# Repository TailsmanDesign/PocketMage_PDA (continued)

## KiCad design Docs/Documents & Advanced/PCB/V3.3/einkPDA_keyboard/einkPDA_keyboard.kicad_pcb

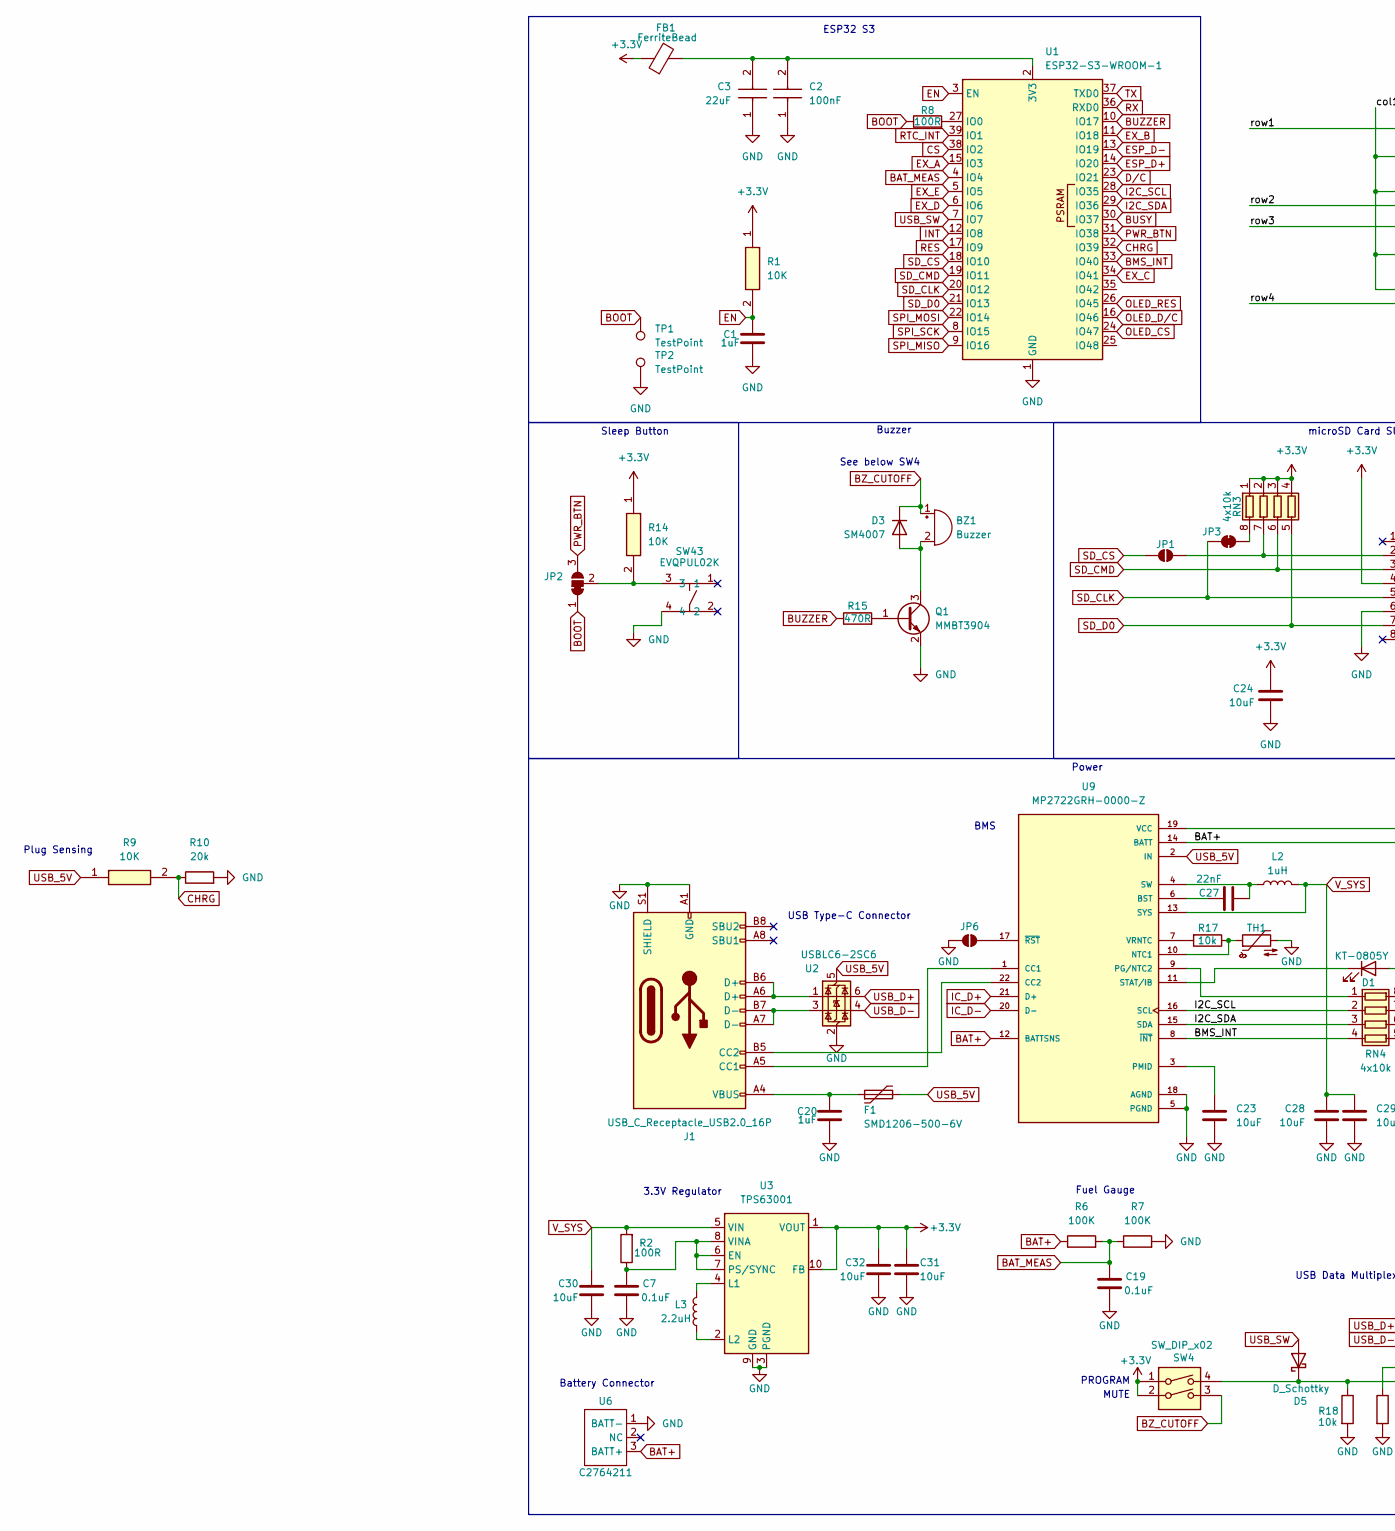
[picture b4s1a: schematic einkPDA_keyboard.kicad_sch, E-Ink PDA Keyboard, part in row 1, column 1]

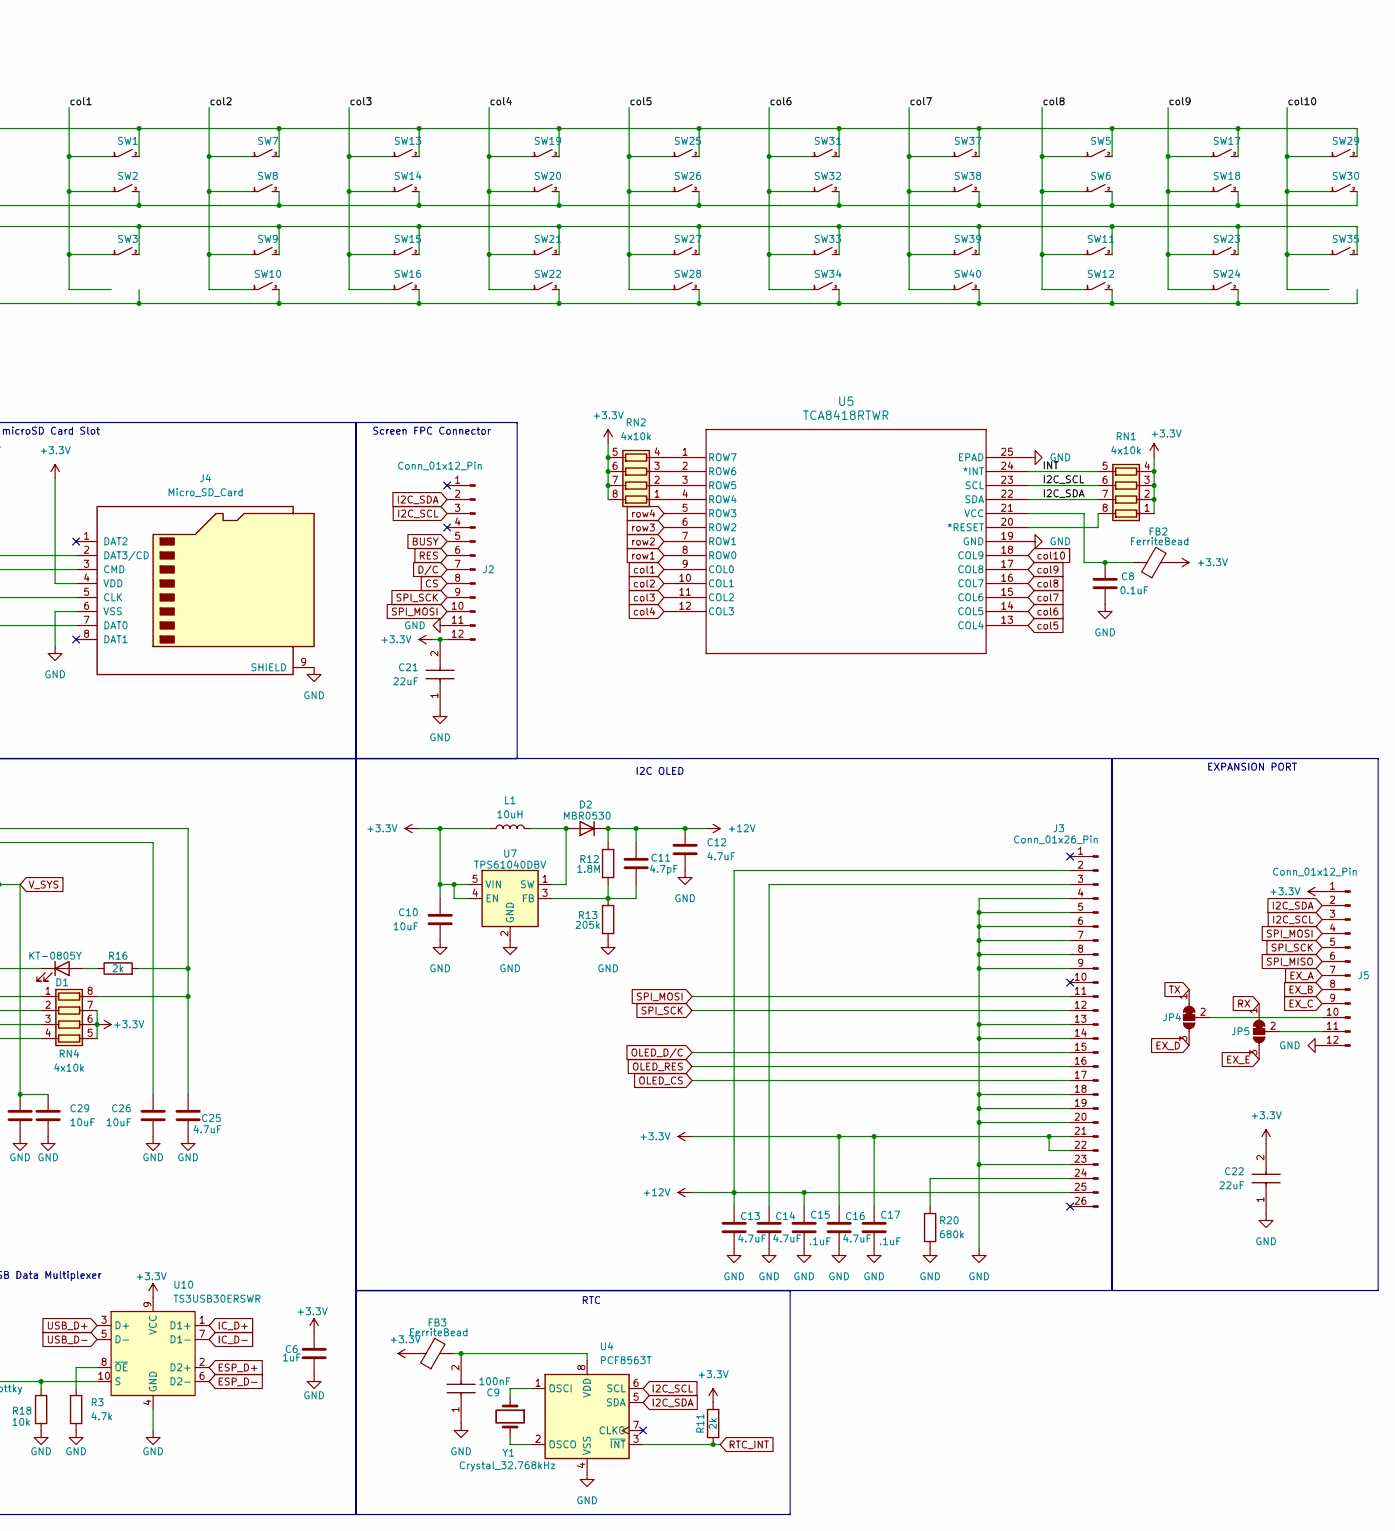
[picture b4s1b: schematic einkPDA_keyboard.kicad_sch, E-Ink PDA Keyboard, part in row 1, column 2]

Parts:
BZ1: Buzzer; BUZ-SMD_3P_L5.0-W5.0-P3.50-TL; LCSC Part # C781883
C1, C6, C20: 1uF; C_0603_1608Metric; LCSC Part # C15849
C2, C9: 100nF; C_0805_2012Metric; Mouser Part Number 603-CC805KRX7R9BB104
C3, C21, C22: 22uF; C_0805_2012Metric; Mouser Part Number 187-CL21A226MAQNNNE
C7, C8, C19: 0.1uF; C_0402_1005Metric; LCSC Part # C1525
C10, C23, C26, C28, C29, C30, C31, C32: 10uF; C_0805_2012Metric; LCSC PART # C15850
C11: 4.7pF; C_0603_1608Metric; LCSC PART # C1669
C12, C13, C14, C16: 4.7uF; C_1206_3216Metric; LCSC PART # C29823
C15, C17: .1uF; C_0805_2012Metric; LCSC PART # C28233
C24: 10uF; C_0805_2012Metric; LCSC Part # C15850
C25: 4.7uF; C_0805_2012Metric; LCSC Part # C1779
C27: 22nF; C_0603_1608Metric; LCSC Part # C21122
D1: KT-0805Y; LED_0805_2012Metric; LCSC Part # C2296
D2: MBR0530; D_SOD-123; LCSC PART # C77336
D3: SM4007; D_SOD-123F; LCSC Part # C64898
D5: D_Schottky; D_SOD-323; LCSC Part # C191023
F1: SMD1206-500-6V; Fuse_1206_3216Metric; LCSC Part # C2760308
FB1, FB2, FB3: FerriteBead; L_0603_1608Metric; LCSC Part # C85831
J1: USB_C_Receptacle_USB2.0_16P; USB-TYPE-C-SMD_TYPE-C-16P-QTWT; LCSC Part # C5187472
J2, J5: Conn_01x12_Pin; AFC01-S12FCA-00; LCSC Part # C262661
J3: Conn_01x26_Pin; FPC-SMD_AFC24-S26FIA [DUAL-SIDE]; LCSC PART # C262684
J4: Micro_SD_Card; TF-SMD_503398-1892; LCSC Part # C428492
JP1, JP6: SolderJumper_2_Open; SolderJumper-2_P1.3mm_Open_RoundedPad1.0x1.5mm
JP2, JP4, JP5: SolderJumper_3_Bridged12; SolderJumper-3_P1.3mm_Bridged12_RoundedPad1.0x1.5mm
JP3: SolderJumper_2_Bridged; SolderJumper-2_P1.3mm_Bridged_RoundedPad1.0x1.5mm
L1: 10uH; L_Chilisin_BMRx00060630; LCSC PART # C5189958
L2: 1uH; L_Ferrocore_DLG-0504; LCSC Part # C2929426
L3: 2.2uH; L_Wurth_WE-LQSH-3012; LCSC Part # C19734
Q1: MMBT3904; SOT-23; LCSC Part # C20526
R1, R9, R14: 10K; R_0805_2012Metric; Mouser Part Number 303-0805W8F1002T5E
R2, R8: 100R; R_0603_1608Metric; LCSC Part # C22775
R3: 4.7k; R_0603_1608Metric; LCSC Part # C23162
R6, R7: 100K; R_0603_1608Metric; LCSC Part # C25803
R10: 20k; R_0603_1608Metric; LCSC Part # C4184
R11, R16: 2k; R_0805_2012Metric; LCSC Part # C17604
R12: 1.8M; R_0805_2012Metric; LCSC PART # C17399
R13: 205k; R_0805_2012Metric; LCSC PART # C218417
R15: 470R; R_0805_2012Metric; LCSC Part # C17710
R17: 10k; R_0805_2012Metric; LCSC Part # C17414
R18: 10k; R_0603_1608Metric; LCSC Part # C25804
R20: 680k; R_0805_2012Metric; LCSC PART # C17797
RN1, RN2, RN3, RN4: 4x10k; R_Array_Concave_4x0603; LCSC Part # C29718
SW1, SW2, SW3, SW5, SW6, SW7, SW8, SW9, SW10, SW11, SW12, SW13, SW14, SW15, SW16, SW17, SW18, SW19, SW20, SW21, SW22, SW23, SW24, SW25, SW26, SW27, SW28, SW29, SW30, SW31, SW32, SW33, SW34, SW35, SW37, SW38, SW39, SW40: contact_pad_SINGLE
SW4: SW_DIP_x02; 2X_DIP_DHN-02-V-TR; LCSC Part # C224995
SW43: EVQPUL02K; SW-SMD_TS24CA; LCSC Part # C393942
TH1: NTC; R_0603_1608Metric; LCSC Part # C76589
TP1, TP2: TestPoint; TestPoint_Pad_1.0x1.0mm
U1: ESP32-S3-WROOM-1; LCSC Part # C2913202
U2: USBLC6-2SC6; SOT-23-6; LCSC Part # C7519
U3: TPS63001; Texas_DRC0010J_ThermalVias; LCSC Part # C28060
U4: PCF8563T; SOIC-8_3.9x4.9mm_P1.27mm; LCSC Part # C7440
U5: TCA8418RTWR; RTW24_2P45X2P45; LCSC Part # C138713
U6: C2764211; JST_PH_2P_P2.00mm; LCSC Part # C2764211
U7: TPS61040DBV; SOT-23-5; LCSC PART # C7722
U9: MP2722GRH-0000-Z; IC_MP2722GRH-0000-Z; PARTREV 1.0; LCSC Part # C20099551
U10: TS3USB30ERSWR; UQFN-10_1.4x1.8mm_P0.4mm; LCSC Part # C73880
Y1: Crystal_32.768kHz; Crystal_SMD_3215-2Pin_3.2x1.5mm; LCSC Part # C5213671

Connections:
+3.3V: C6.2, C10.2, C16.1, C17.1, C21.2, C22.2, C24.1, C31.2, C32.2, FB1.1, FB2.2, FB3.1, J2.12, J3.21, J3.22, J4.4 (VDD), J5.1, L1.1, R1.1, R11.2, R14.1, RN1.1 (R1.1), RN1.2 (R2.1), RN1.3 (R3.1), RN1.4 (R4.1), RN2.5 (R4.2), RN2.6 (R3.2), RN2.7 (R2.2), RN2.8 (R1.2), RN3.1 (R1.1), RN3.2 (R2.1), RN3.3 (R3.1), RN3.4 (R4.1), RN4.5 (R4.2), RN4.6 (R3.2), RN4.7 (R2.2), SW4.1, SW4.2, U3.1 (VOUT), U3.10 (FB), U7.4 (EN), U7.5 (VIN), U10.9 (VCC)
+12V: C11.2, C12.1, C13.1, C15.1, D2.1 (K), J3.2, J3.25, R12.1
BAT+: C26.2, R6.1, U6.3 (BATT+), U9.12 (BATTSNS), U9.14 (BATT)
BAT_MEAS: C19.1, R6.2, R7.1, U1.4 (IO4)
BMS_INT: RN4.4 (R4.1), U1.33 (IO40), U9.8 (~INT)
BOOT: JP2.1 (A), R8.1, TP1.1
BUSY: J2.5, U1.30 (IO37)
BUZZER: R15.1, U1.10 (IO17)
BZ_CUTOFF: BZ1.1 (+), D3.1 (K), SW4.3
CHRG: R9.2, R10.1, U1.32 (IO39)
CS: J2.8, U1.38 (IO2)
D/C: J2.7, U1.23 (IO21)
EN: C1.2, R1.2, U1.3 (EN)
ESP_D+: U1.14 (IO20), U10.2 (D2+)
ESP_D-: U1.13 (IO19), U10.6 (D2-)
EX_A: J5.7, U1.15 (IO3)
EX_B: J5.8, U1.11 (IO18)
EX_C: J5.9, U1.34 (IO41)
EX_D: JP4.3 (B), U1.6 (IO6)
EX_E: JP5.3 (B), U1.5 (IO5)
GND: C1.1, C2.1, C3.1, C6.1, C7.2, C8.2, C9.1, C10.1, C12.2, C13.2, C14.2, C15.2, C16.2, C17.2, C19.2, C20.1, C21.1, C22.1, C23.1, C24.2, C25.2, C26.1, C28.1, C29.1, C30.1, C31.1, C32.1, J1.A1 (GND), J1.A12 (GND), J1.B1 (GND), J1.B12 (GND), J1.S1 (SHIELD), J2.11, J3.4, J3.5, J3.6, J3.7, J3.8, J3.9, J3.13, J3.14, J3.18, J3.19, J3.20, J3.23, J4.6 (VSS), J4.9 (SHIELD), J5.12, JP6.1 (A), Q1.2 (E), R3.2, R7.2, R10.2, R13.2, R18.2, R20.2, SW43.4, TH1.2, TP2.1, U1.1 (GND), U1.40 (GND), U1.41 (GND), U2.2 (GND), U3.3 (PGND), U3.9 (GND), U3.11 (PGND), U4.4 (VSS), U5.19 (GND), U5.25 (EPAD), U5.V, U6.1 (BATT-), U7.2 (GND), U9.5 (PGND), U9.18 (AGND), U10.4 (GND)
I2C_SCL: J2.3, J5.3, RN1.6 (R3.2), RN4.2 (R2.1), U1.28 (IO35), U4.6 (SCL), U5.23 (SCL), U9.16 (SCL)
I2C_SDA: J2.2, J5.2, RN1.7 (R2.2), RN4.3 (R3.1), U1.29 (IO36), U4.5 (SDA), U5.22 (SDA), U9.15 (SDA)
IC_D+: U9.21 (D+), U10.1 (D1+)
IC_D-: U9.20 (D-), U10.7 (D1-)
INT: RN1.5 (R4.2), U1.12 (IO8), U5.24 (*INT)
unnamed: BZ1.2 (-), D3.2 (A), Q1.3 (C)
unnamed: C20.2, F1.1, J1.A4 (VBUS), J1.A9 (VBUS), J1.B4 (VBUS), J1.B9 (VBUS)
unnamed: D1.2 (A), R16.1
unnamed: D1.1 (K), U9.11 (STAT/IB)
unnamed: D2.2 (A), L1.2, U7.1 (SW)
unnamed: D5.1 (K), R18.1, SW4.4, U10.10 (S)
unnamed: J1.A5 (CC1), U9.1 (CC1)
unnamed: J1.B5 (CC2), U9.22 (CC2)
unnamed: J1.A6 (D+), J1.B6 (D+), U2.1 (I/O1)
unnamed: J1.A7 (D-), J1.B7 (D-), U2.3 (I/O2)
unnamed: C14.1, J3.3
unnamed: J3.24, R20.1
unnamed: J4.2 (DAT3/CD), JP1.2 (B), RN3.7 (R2.2)
unnamed: J5.10, JP4.2 (C)
unnamed: J5.11, JP5.2 (C)
unnamed: JP2.2 (C), R14.2, SW43.3
unnamed: JP3.2 (B), RN3.8 (R1.2)
unnamed: JP6.2 (B), U9.17 (~RST)
unnamed: Q1.1 (B), R15.2
unnamed: RN1.8 (R1.2), U5.20 (*RESET)
unnamed: RN2.1 (R1.1), U5.4 (ROW4)
unnamed: RN2.2 (R2.1), U5.3 (ROW5)
unnamed: RN2.3 (R3.1), U5.2 (ROW6)
unnamed: RN2.4 (R4.1), U5.1 (ROW7)
unnamed: RN4.1 (R1.1), U9.9 (PG/NTC2)
unnamed: C25.1, R16.2, RN4.8 (R1.2), U9.19 (VCC)
unnamed: C2.2, C3.2, FB1.2, U1.2 (3V3)
unnamed: R8.2, U1.27 (IO0)
unnamed: C7.1, R2.1, U3.6 (EN), U3.7 (PS/SYNC), U3.8 (VINA)
unnamed: L3.1, U3.4 (L1)
unnamed: L3.2, U3.2 (L2)
unnamed: U4.1 (OSCI), Y1.1
unnamed: U4.2 (OSCO), Y1.2
unnamed: C9.2, FB3.2, U4.8 (VDD)
unnamed: C8.1, FB2.1, U5.21 (VCC)
unnamed: C11.1, R12.2, R13.1, U7.3 (FB)
unnamed: C27.2, U9.6 (BST)
unnamed: R17.1, TH1.1, U9.10 (NTC1)
unnamed: C23.2, U9.3 (PMID)
unnamed: C27.1, L2.1, U9.4 (SW)
unnamed: R17.2, U9.7 (VRNTC)
unnamed: R3.1, U10.8 (~OE)
OLED_CS: J3.17, U1.24 (IO47)
OLED_D/C: J3.15, U1.16 (IO46)
OLED_RES: J3.16, U1.26 (IO45)
PWR_BTN: JP2.3 (B), U1.31 (IO38)
RES: J2.6, U1.17 (IO9)
RTC_INT: R11.1, U1.39 (IO1), U4.3 (~INT)
RX: JP5.1 (A), U1.36 (RXD0)
SD_CLK: J4.5 (CLK), JP3.1 (A), U1.20 (IO12)
SD_CMD: J4.3 (CMD), RN3.6 (R3.2), U1.19 (IO11)
SD_CS: JP1.1 (A), U1.18 (IO10)
SD_D0: J4.7 (DAT0), RN3.5 (R4.2), U1.21 (IO13)
SPI_MISO: J5.6, U1.9 (IO16)
SPI_MOSI: J2.10, J3.11, J5.4, U1.22 (IO14)
SPI_SCK: J2.9, J3.12, J5.5, U1.8 (IO15)
TX: JP4.1 (A), U1.37 (TXD0)
USB_5V: F1.2, R9.1, U2.5 (VBUS), U9.2 (IN)
USB_D+: U2.6 (I/O1), U10.3 (D+)
USB_D-: U2.4 (I/O2), U10.5 (D-)
USB_SW: D5.2 (A), U1.7 (IO7)
V_SYS: C28.2, C29.2, C30.2, L2.2, R2.2, U3.5 (VIN), U9.13 (SYS)
col1: SW1.1, SW2.1, SW3.1, U5.9 (COL0)
col2: SW7.1, SW8.1, SW9.1, SW10.1, U5.10 (COL1)
col3: SW13.1, SW14.1, SW15.1, SW16.1, U5.11 (COL2)
col4: SW19.1, SW20.1, SW21.1, SW22.1, U5.12 (COL3)
col5: SW25.1, SW26.1, SW27.1, SW28.1, U5.13 (COL4)
col6: SW31.1, SW32.1, SW33.1, SW34.1, U5.14 (COL5)
col7: SW37.1, SW38.1, SW39.1, SW40.1, U5.15 (COL6)
col8: SW5.1, SW6.1, SW11.1, SW12.1, U5.16 (COL7)
col9: SW17.1, SW18.1, SW23.1, SW24.1, U5.17 (COL8)
col10: SW29.1, SW30.1, SW35.1, U5.18 (COL9)
row1: SW1.2, SW5.2, SW7.2, SW13.2, SW17.2, SW19.2, SW25.2, SW29.2, SW31.2, SW37.2, U5.8 (ROW0)
row2: SW2.2, SW6.2, SW8.2, SW14.2, SW18.2, SW20.2, SW26.2, SW30.2, SW32.2, SW38.2, U5.7 (ROW1)
row3: SW3.2, SW9.2, SW11.2, SW15.2, SW21.2, SW23.2, SW27.2, SW33.2, SW35.2, SW39.2, U5.6 (ROW2)
row4: SW10.2, SW12.2, SW16.2, SW22.2, SW24.2, SW28.2, SW34.2, SW40.2, U5.5 (ROW3)

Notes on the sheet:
Plug Sensing
ESP32 S3
RTC
Screen FPC Connector
PROGRAM
Buzzer
Battery Connector
See below SW4
Power
microSD Card Slot
Fuel Gauge
USB Data Multiplexer
USB Type-C Connector
3.3V Regulator
EXPANSION PORT
Sleep Button
MUTE
BMS
I2C OLED

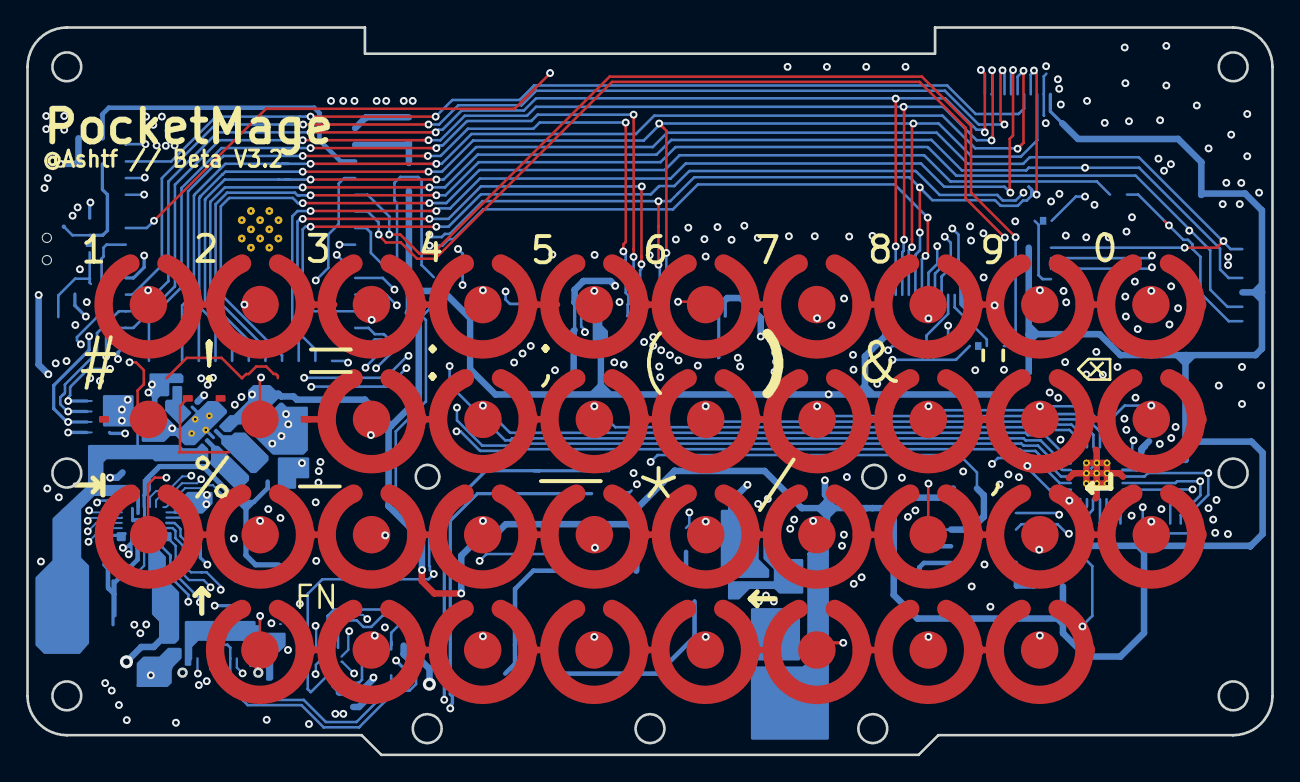
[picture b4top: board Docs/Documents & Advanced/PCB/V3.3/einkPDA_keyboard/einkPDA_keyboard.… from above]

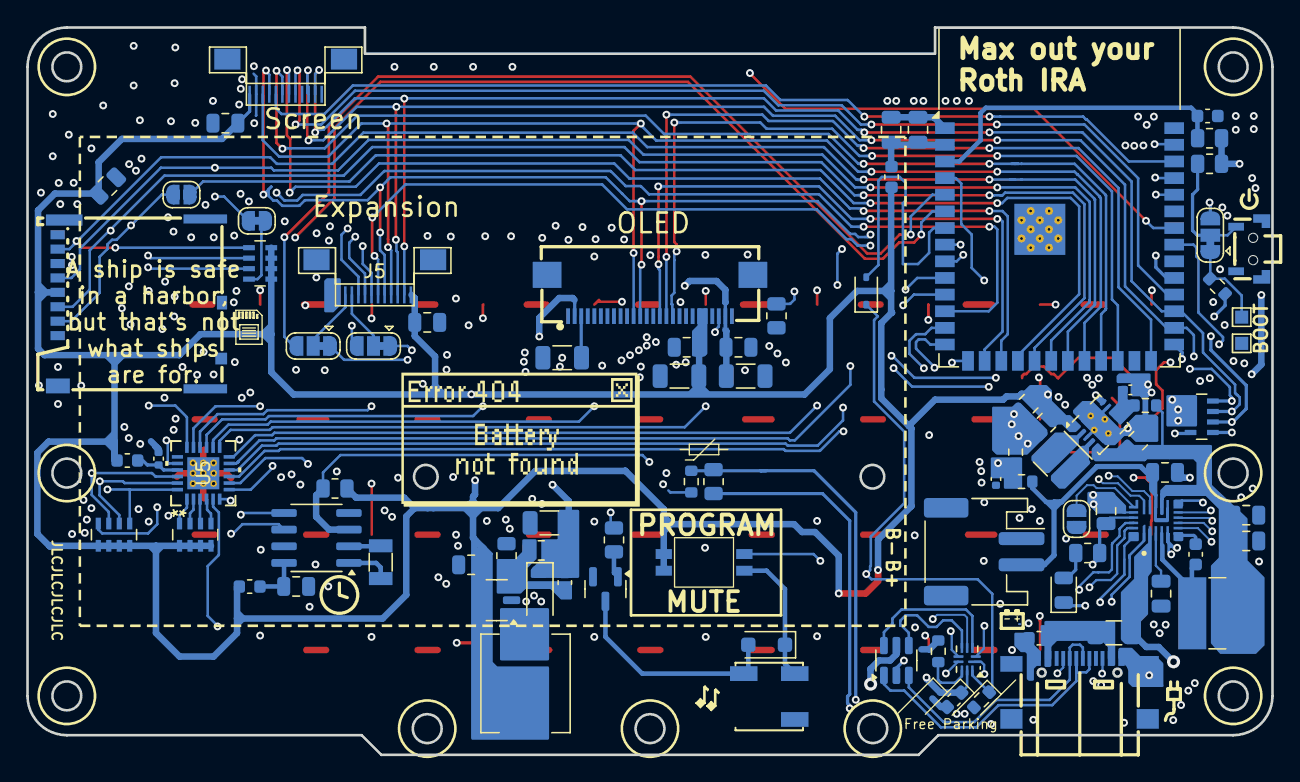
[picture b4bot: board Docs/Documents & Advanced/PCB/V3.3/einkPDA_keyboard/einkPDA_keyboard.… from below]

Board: 4 copper layers, 95.0 x 55.5 mm, 125 parts (87 on the bottom side), 101 nets.

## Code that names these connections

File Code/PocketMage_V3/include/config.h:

#ifndef CONFIG_H
#define CONFIG_H

// OTA App
// Is this an OTA APP? // OTA_APP: set -DOTA_APP_FLAG=1 in platformio.ini
#if OTA_APP_FLAG
#define OTA_APP true
#else
#define OTA_APP false
#endif

// CONFIGURATION & SETTINGS
////////////////////////////////////////////////////////////////////////////////////////////////////////////////////////////|
#define KB_COOLDOWN 3                           // Keypress cooldown
#define MAX_FILES 10                            // Number of files to store
#define FORMAT_SPIFFS_IF_FAILED true            // Format the SPIFFS filesystem if mount fails
#define SLEEPMODE "TEXT"                        // TEXT, SPLASH, CLOCK
#define TXT_APP_STYLE 1                         // 0: Old Style (NOT SUPPORTED), 1: New Style
#define SET_CLOCK_ON_UPLOAD false               // Should system clock be set automatically on code upload?
#define TOUCH_TIMEOUT_MS 1200                   // Delay after scrolling to return to typing mode (ms)
#define SYS_METADATA_FILE "/sys/SDMMC_META.txt" // File path to the file system metadata file
#define POWER_SAVE_FREQ 40                      // CPU freq for power save mode
#define IDLE_TIME 20000                         // time to wait for mage idle (ms)

// Full refresh after N partial refreshes (CHANGE WITH CAUTION)
#if POCKETMAGE_HW_VERSION == 2
  #define FULL_REFRESH_AFTER 10 // Prod uses N=10                    
#else
  #define FULL_REFRESH_AFTER 5  // Beta needs N=5
#endif
////////////////////////////////////////////////////////////////////////////////////////////////////////////////////////////|

// PIN DEFINITION
#define I2C_SCL       35
#define I2C_SDA       36
#define SWITCHED_I2C_SDA  42
#define SWITCHED_I2C_SCL  48
#define MPR121_ADDR   0x5A
#define MP2722_ADDR   0x3F
#define USB_MUX_PIN   7

#define KB_IRQ        8
#define PWR_BTN       0 
#define BAT_SENS      4
#define CHRG_SENS     39
#define RTC_INT       1 
#define LOAD_SWITCH   38

// SPI
#define SPI_MOSI      14
#define SPI_SCK       15

// OLED
#define OLED_CS       47
#define OLED_DC       46
#define OLED_RST      45

// E Ink
#define EPD_CS        2
#define EPD_DC        21
#define EPD_RST       9
#define EPD_BUSY      37

// SDMMC mode
#define SD_CLK        12
#define SD_CMD        11
#define SD_D0         13
#define SD_D1         5
#define SD_D2         6
#define SD_D3         10

// SDSPI mode
#define SD_CS         10
#define SD_MOSI       11
#define SD_SCK        12
#define SD_MISO       13

#define BZ_PIN        17

// ===================== SYSTEM SETTINGS =====================
// Persistent preferences
extern int TIMEOUT;              // Auto sleep timeout (seconds)
extern bool DEBUG_VERBOSE;       // Extra debug output
extern bool SYSTEM_CLOCK;        // Show clock on screen
extern bool SHOW_YEAR;           // Show year in clock
extern bool SAVE_POWER;          // Enable power saving mode
extern bool ALLOW_NO_MICROSD;    // Allow running without SD card
extern bool HOME_ON_BOOT;        // Start home app on boot
extern int OLED_BRIGHTNESS;      // OLED brightness (0-255)
extern int OLED_MAX_FPS;         // OLED max FPS
extern bool SD_SPI_COMPATIBILITY;

#endif

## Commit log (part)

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2025-08-21 Added coin flip command and echo command :D
2025-09-07 Updated FileWiz
2025-12-11 chore(pages): deploy docs from run 16 b4a7622bd21c27e3b907839c7363c631d1cff61b
2025-12-11 chore(pages): deploy docs from run 17 b46548cb70e74629836d85ba346bb06107bdb5df
2025-12-11 chore(pages): deploy docs from run 18 03e5442111f553fd244e87bc8354e290279162f6
2025-12-11 chore(pages): deploy docs from run 19 3da2547743af0e05953c001742ab1c8ec4873808
2025-12-12 chore(pages): deploy docs from run 20 fc906b50399f80466a70593574735f3cf63ca9e4
2025-12-12 chore(pages): deploy docs from run 22 d3be530fab8d317c775d4df800b196a16523d874
2025-12-12 chore(pages): deploy docs from run 23 a3d5cef390fe24d48c37a8f76d319da993470a29
2025-12-17 chore(pages): deploy docs from run 24 bdd2dd64cfa319870193a13f1baea563de97a0d9
2025-12-19 Reorder to possibly fix issue #60
2025-12-19 remove function
2025-12-19 chore(pages): deploy docs from run 25 031486b734dd07ec120ebf7bb6da17052393933b
2025-12-23 chore(pages): deploy docs from run 26 023821e6a468b099c5eae62f6f86bd6a32603942
2025-12-23 chore(pages): deploy docs from run 27 33a097bf41ea17b2a93b0551c162f93a61b805c7
2025-12-23 chore(pages): deploy docs from run 28 63ec2bf12c98a235b128f8973c7c1837790bb064
2025-12-23 chore(pages): deploy docs from run 29 cefb973ac47048903d9619e0ae818144b031fd73
2025-12-23 chore(pages): deploy docs from run 30 cefb973ac47048903d9619e0ae818144b031fd73
2025-12-24 chore(pages): deploy docs from run 31 8e439f621f9f5c2e3008882723340cfe866f164e
2025-12-24 Add option for new file
2025-12-24 chore(pages): deploy docs from run 32 c4d67baa466fe8e3d0422c5fc8d3e7fe630d7a68
2025-12-24 chore(pages): deploy docs from run 33 2daa772eb4eda0672195e1676b6784c4ee39cc63
2025-12-24 chore(pages): deploy docs from run 34 2daa772eb4eda0672195e1676b6784c4ee39cc63
2025-12-30 chore(pages): deploy docs from run 35 c40f269ce35e6b8cf1daca732c852dffaab7d901
2025-12-31 added blank app workflow
    my pedantic Latin suggestion: "Fabricam Magicam Ordinationis Creare", this way the device we are creating is magical, rather than the organization. also, moves verb to end per SOV order and makes the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
2025-12-31 fix blankapp build temporarily
2026-01-02 chore(pages): deploy docs from run 36 c599c3a69a2619a78e5a6eb1b78038bf1806171f
2026-01-02 chore(pages): deploy docs from run 37 85a6bce2dcf945ac847eaff199890e31ebff4759
2026-01-02 chore(pages): deploy docs from run 38 6ba2b1eb80c78503f0eded2884f5afbd2b83d077
2026-01-02 chore(pages): deploy docs from run 39 241f09ee7b8aadac74aeca9f9bd670884eb510de
2026-01-04 chore(pages): deploy docs from run 40 4491f5f3365c4070e810780c00e18684c54a2f7c
2026-01-22 chore(pages): deploy docs from run 41 848e1f4fdac9454e3a451cd5b6b19d39790514f8
2026-01-31 chore(pages): deploy docs from run 42 b3f920c980e13cf9ef62ac6966c4e7ab05732cc7
2026-01-31 chore(pages): deploy docs from run 43 b3f920c980e13cf9ef62ac6966c4e7ab05732cc7
2026-01-31 chore(pages): deploy docs from run 44 567786d4b93395423eba499aca9a35d08ab8724a
2026-01-31 chore(pages): deploy docs from run 45 bf8c62eea4f43b75405bdf48c60900458f5890ac
2026-01-31 chore(pages): deploy docs from run 46 842057136d8108bf77f8caf0400b15b2826a3703
2026-01-31 chore(pages): deploy docs from run 47 f2c3a0c1a46ccb8477036a970e9f907541a2aabb
2026-02-01 Update script sources to use unpkg instead of jsdelivr as a test
2026-02-01 chore(pages): deploy docs from run 48 a0c1661f02db0eaba110b934285a0cbbdf7bc5d0
2026-02-01 SHFT -> SHIFT
2026-02-01 Update genral keys, add keymap
2026-02-02 Update for added oled edit keys
2026-02-04 chore(pages): deploy docs from run 49 528f4eadc39e6e4cd2739bdb43b95a9bec89a8b2
2026-02-06 chore(pages): deploy docs from run 50 3c093467510f041bc0b870a8d3083b79499e6b8b
2026-02-08 chore(pages): deploy docs from run 51 30f2cc993c400894f42e61e2b3cf08741eafb8aa
2026-02-12 Remove old dev versions from manifest
2026-02-12 chore(pages): deploy docs from run 52 7a74166bcbf4d4ecf91e45f740b3b63309711e9a
2026-02-12 chore(pages): deploy docs from run 53 bf61f96223a4ada0631ab8b14d849dceda4f6298
2026-02-12 chore(pages): deploy docs from run 54 6942f49592b48ee400d6f9acb60ea95eb5d00e06
2026-02-26 chore(pages): deploy docs from run 56 0bda9e6bb0635247c44c614594b15b7790580701
2026-03-03 chore(pages): deploy docs from run 57 7c34336bb57eb6518a24f46b890a200fe4828707
2026-03-04 ical import improvements, new calendar struct
2026-03-05 ui fix and format
2026-03-07 chore(pages): deploy docs from run 58 d5e52ced742333d1d8d963a923f4edfd0e45bc38
2026-03-08 chore(pages): deploy docs from run 59 3a13d8ba90a11341043d2d0eab10929fc5f49cae
2026-03-09 chore(pages): deploy docs from run 60 88d0f1aabd764d1de92a0bb5b2446291454ccc68
2026-03-09 chore(pages): deploy docs from run 61 1a06e25a4555cc301bc8ba1d786488cc23cf75e0
2026-03-09 chore(pages): deploy docs from run 62 d7ab454b1d5f6a21b0c320b40dc2ce7d60605c2b
2026-03-12 chore(pages): deploy docs from run 66 1deb6a2c77711a009c371b126db59bbcd0794cf4
2026-03-20 chore(pages): deploy docs from run 68 c14ead12699fd400d874c7ccb66a62e550faa88e
2026-03-20 chore(pages): deploy docs from run 69 15bc6b1a6532b6c71fbcf5911307dc8f25e3fa74
2026-03-20 chore(pages): deploy docs from run 70 44497f70ef32b6fba8cbd5da21c1a1d06e397348
2026-03-20 chore(pages): deploy docs from run 71 2604d79090b87f8f3b79b9f9bcb2305249c78247
2026-03-25 chore(pages): deploy docs from run 72 2187b1737d6e678a8b76b8ba0c2b36fa4155d54c
2026-03-26 chore(pages): deploy docs from run 73 b4ccf9f752592ead14944526da95f25ac80c6569
2026-03-29 Remove old TXT
2026-03-29 chore(pages): deploy docs from run 74 7d8258722358a65d13a6ca297cd886771dbb3b22
2026-03-29 chore(pages): deploy docs from run 75 7b0e3a2d20a0e14b8b98c3b3d343b61004295d22
2026-03-29 Add detailed fail messages for USB
2026-03-30 chore(pages): deploy docs from run 76 289c5cb8dc40f506e014c7fabd2b29a466789e74
2026-03-30 feat(calendar): add option for weeks to start on Monday
    Adds WEEK_START_MONDAY setting (weekstart t/f in Settings).
    Adjusts Month view grid offset, Week view anchor, and day navigation.
    Day-of-week headers are overlaid and redrawn programmatically
    when Monday-start is enabled.
    Closes #120
2026-03-31 chore(pages): deploy docs from run 77 bf024b0b8a8f10d3f5d5062a9a178dd345785cd4
2026-04-02 PCB updates
2026-04-03 PCB V3.3
2026-04-07 Update issue templates
2026-04-07 Keyboard softlock patch
2026-04-07 chore(pages): deploy docs from run 78 44397e87d1d356b8007ff6f0d9edd6edb5134a1c
2026-04-07 Fix sleep input bug
2026-04-07 Polish
2026-04-08 chore(pages): deploy docs from run 79 4eb00cda116bd0f395b242911d140524f891d438
2026-04-09 Update PCBs
2026-04-09 Update build-firmware.yml for PocketMage release process
2026-04-09 chore(pages): deploy docs from run 80 80d0451723764d73f60c0a8a48fd06d864e03c85
2026-04-09 chore(pages): deploy docs from run 320 1a7053a723ac7f4fea3620d9b2b3823b1a809a5b
2026-04-13 Fix critical battery charge current bug
2026-04-13 chore(pages): deploy docs from run 321 94602574947528b8bca8490f7b38919703105383
2026-04-13 Enhance firmware flashing with hardware selection
    Added hardware selection functionality and updated firmware fetching logic to accommodate hardware-specific paths.
2026-04-13 chore(pages): deploy docs from run 84 78b7b9a70ce3f88e485e875e1c16883ba34f752b
2026-04-13 chore(pages): deploy docs from run 322 78b7b9a70ce3f88e485e875e1c16883ba34f752b
2026-04-13 chore(pages): deploy docs from run 85 00a8f17bf027b3e9cba833515dee47ed584ce455
2026-04-13 chore(pages): deploy docs from run 323 28e3df77d5985440a28e17c703ec1e629bb68044
2026-04-13 chore(pages): deploy docs from run 86 28e3df77d5985440a28e17c703ec1e629bb68044
2026-04-13 chore(pages): deploy docs from run 324 94602574947528b8bca8490f7b38919703105383
2026-04-13 chore(pages): deploy docs from run 89 ac3bffb060f195ad13de65e799b2b04e967a8de5
2026-04-16 Add placeholder app icon
2026-04-19 Implement Repeat Code GUI
2026-04-19 chore(pages): deploy docs from run 90 34f239870144b9cb68dec20ffba14046b375eb82
2026-04-19 chore(pages): deploy docs from run 325 34f239870144b9cb68dec20ffba14046b375eb82
2026-04-21 Implement Mesh-NOW lib
    Thanks NellowTCS!
2026-04-21 Fix OTA_APP compile errors
2026-04-25 Deploy Docs 413f97003c317ab9fdc61293f8d658c3a7830867
2026-04-26 Add README.md for PocketMage documentation
    Added comprehensive documentation for the PocketMage PDA project, including local development instructions and contributing guidelines.
2026-04-26 Deploy Docs c81ac4ece1662fa3fcc92e91be4d8c0619c779fe
2026-04-26 Clarify OTA_APP build instructions in APP_TEMPLATE.cpp
    Updated comments for clarity on OTA_APP build instructions.
2026-04-27 Deploy Docs 292a06b1ef0897cd8e253b947ed406a31553926b
2026-04-27 Deploy Docs 578df5a3c28a14442ded11bdc0c36fb4de1ccb96
2026-04-27 Deploy Docs 0dbc60d00ea49e741ec69a5504b45ea83f98bd2e
2026-04-27 Add potion link and unlink
    Link and unlink phrases to run potion programs.
    pot link <filename>.c <phrase>
    pot unlink <phrase>
2026-05-02 Update wiring for load switch
2026-05-03 Rename Folder
2026-05-03 Fix startup issue for production boards
2026-05-03 Refine Terminal customization
2026-05-03 Deploy Docs 1d3c74bcd4ef88d89d4f85bf588ea24d6d009bd8
2026-05-09 chore(pages): deploy docs from run 327 0498a123540d24a53edf021e9c4ec0959c58dabb
2026-05-16 Deploy Docs 0498a123540d24a53edf021e9c4ec0959c58dabb
2026-05-25 chore(pages): deploy docs from run 328 f85b23cacfd84259249487ce8f2a31a89e479e0c
2026-05-25 chore(pages): deploy docs from run 91 f85b23cacfd84259249487ce8f2a31a89e479e0c
2026-06-01 Deploy Docs 765ff3714f12358691ca13a2536e2c196d3278df
2026-06-15 Some improvements IDK, this worked for me a bit, might update
2026-06-17 Inline code markdown support
    closes #265
2026-06-17 Chat app working
2026-06-17 Fix font rendering
2026-06-17 Fix fonts
2026-06-17 Bug fixes and the like
2026-06-21 Deploy Docs 6d2df98c7164592a72744a121b1283412a65259c
2026-06-21 Deploy Docs c28f7ae56337e9ef63c3bcc4ce4d7a6259ca0394
